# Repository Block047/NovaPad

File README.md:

# NovaPad

NovaPad is a fully customizable and open sourced macropad that I had designed for fun in my spare time.

NovaPad was designed as a multi-purpose tool, allowing for it to aid in any task at hand.

## Features
Fully customizable:
 - EC11 Rotary Encoder Switch
 - 6 Keys
 - WS2812B RGB LED's for each key
 - 128x32 OLED screens 

## Housing
The housing is split into two parts, the top lid of the case, and the lower case itself.
The PCB is secured to the case using two M3 heated inserts vertically, and the lid is secured to the case using three horizontal self-tapping screws.

Made in OnShape

## PCB

The PCB intergrates the various components included in the project, allowing them to communicate with one another, giving the keyboard its functionality.
Designing the PCB consisted of organizing the components in the positions that I wanted them in, and then drawing the trace lines, which took hours of work left untracked in hacktime (I was trying to use wakatime to track it, which ended up not working.)

## Schematic

The schematic had been the easiest part of the project, only specifying what connected to what.
The only decently difficult part of designing the schematic was figuring out where and how to get the footprints for the various components that KiCad didn't have, and figuring out how to wire the keyboard matrix.

## Firmware
This project uses KMK python code, running on the XIAO microcontroller provided by stardance flashed with CircuitPython.
The firmware leaves much for customization, the default functions only being a simple number pad with a volume knob, the OLED displaying "NovaPad".
This configuration was designed to be customized, giving the user flexability and functionality when needed.

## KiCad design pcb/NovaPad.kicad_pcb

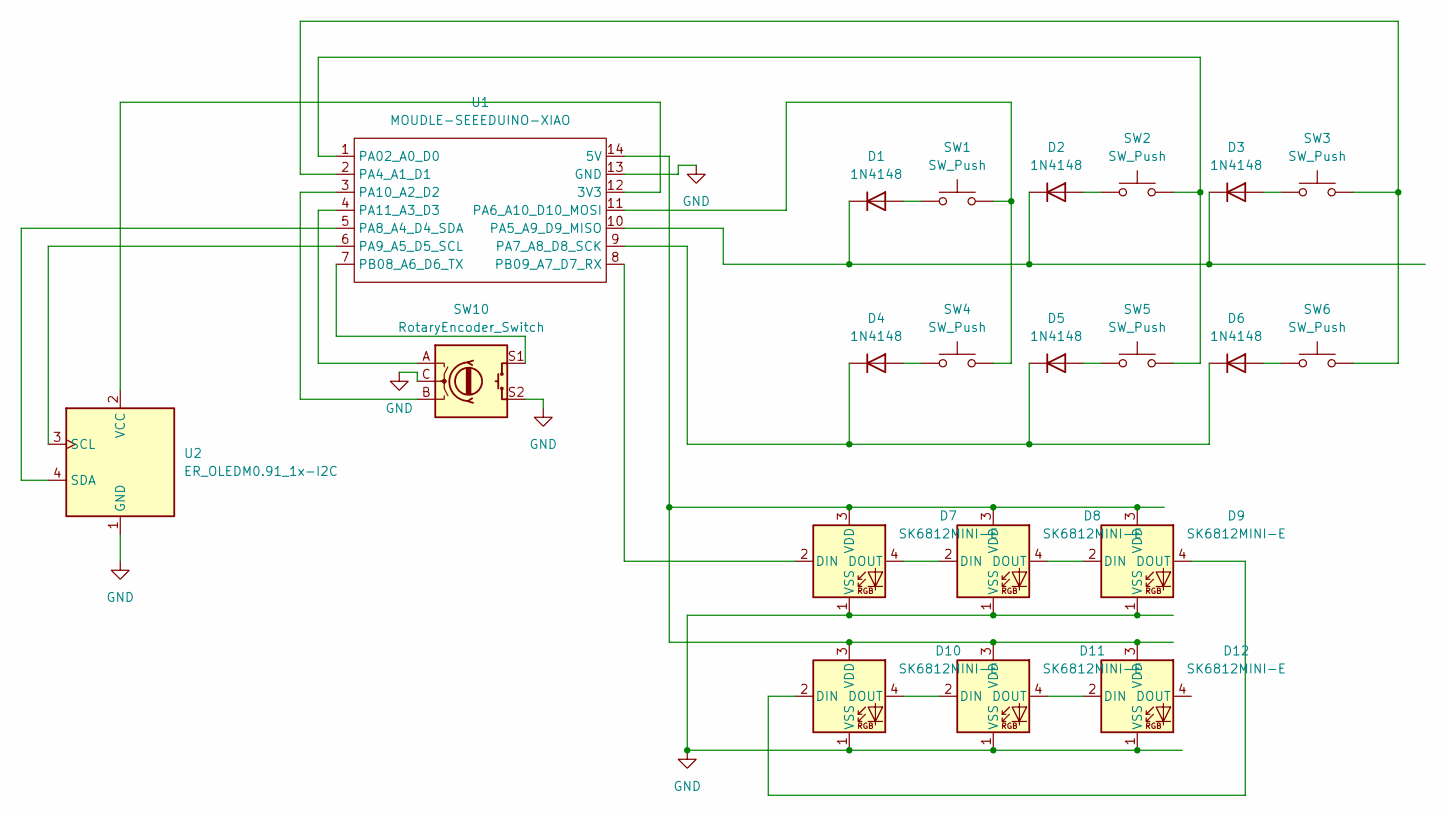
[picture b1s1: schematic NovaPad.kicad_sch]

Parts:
D1, D2, D3, D4, D5, D6: 1N4148; D_DO-35_SOD27_P7.62mm_Horizontal
D7, D8, D9, D10, D11, D12: SK6812MINI-E; LED_SK6812MINI-E_3.2x2.8mm_P1.5mm_ReverseMount
SW1, SW2, SW3, SW4, SW5, SW6: SW_Push; SW_Cherry_MX_1.00u_PCB
SW10: RotaryEncoder_Switch; RotaryEncoder_Alps_EC11E-Switch_Vertical_H20mm
U1: MOUDLE-SEEEDUINO-XIAO; XIAO-Generic-Hybrid-14P-2.54-21X17.8MM
U2: ER_OLEDM0.91_1x-I2C

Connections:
GND: D7.1 (VSS), D8.1 (VSS), D9.1 (VSS), D10.1 (VSS), D11.1 (VSS), D12.1 (VSS), SW10.C, SW10.S2, U1.13 (GND), U2.1 (GND)
unnamed: D1.2 (A), SW1.1
unnamed: D1.1 (K), D2.1 (K), D3.1 (K), U1.10 (PA5_A9_D9_MISO)
unnamed: D2.2 (A), SW2.1
unnamed: D3.2 (A), SW3.1
unnamed: D4.2 (A), SW4.1
unnamed: D4.1 (K), D5.1 (K), D6.1 (K), U1.9 (PA7_A8_D8_SCK)
unnamed: D5.2 (A), SW5.1
unnamed: D6.2 (A), SW6.1
unnamed: D7.2 (DIN), U1.8 (PB09_A7_D7_RX)
unnamed: D7.4 (DOUT), D8.2 (DIN)
unnamed: D8.4 (DOUT), D9.2 (DIN)
unnamed: D9.4 (DOUT), D10.2 (DIN)
unnamed: D10.4 (DOUT), D11.2 (DIN)
unnamed: D7.3 (VDD), D8.3 (VDD), D9.3 (VDD), D10.3 (VDD), D11.3 (VDD), D12.3 (VDD), U1.14 (5V)
unnamed: D11.4 (DOUT), D12.2 (DIN)
unnamed: U1.12 (3V3), U2.2 (VCC)
unnamed: SW2.2, SW5.2, U1.1 (PA02_A0_D0)
unnamed: SW3.2, SW6.2, U1.2 (PA4_A1_D1)
unnamed: SW1.2, SW4.2, U1.11 (PA6_A10_D10_MOSI)
unnamed: U1.5 (PA8_A4_D4_SDA), U2.4 (SDA)
unnamed: U1.6 (PA9_A5_D5_SCL), U2.3 (SCL)
unnamed: SW10.B, U1.3 (PA10_A2_D2)
unnamed: SW10.A, U1.4 (PA11_A3_D3)
unnamed: SW10.S1, U1.7 (PB08_A6_D6_TX)

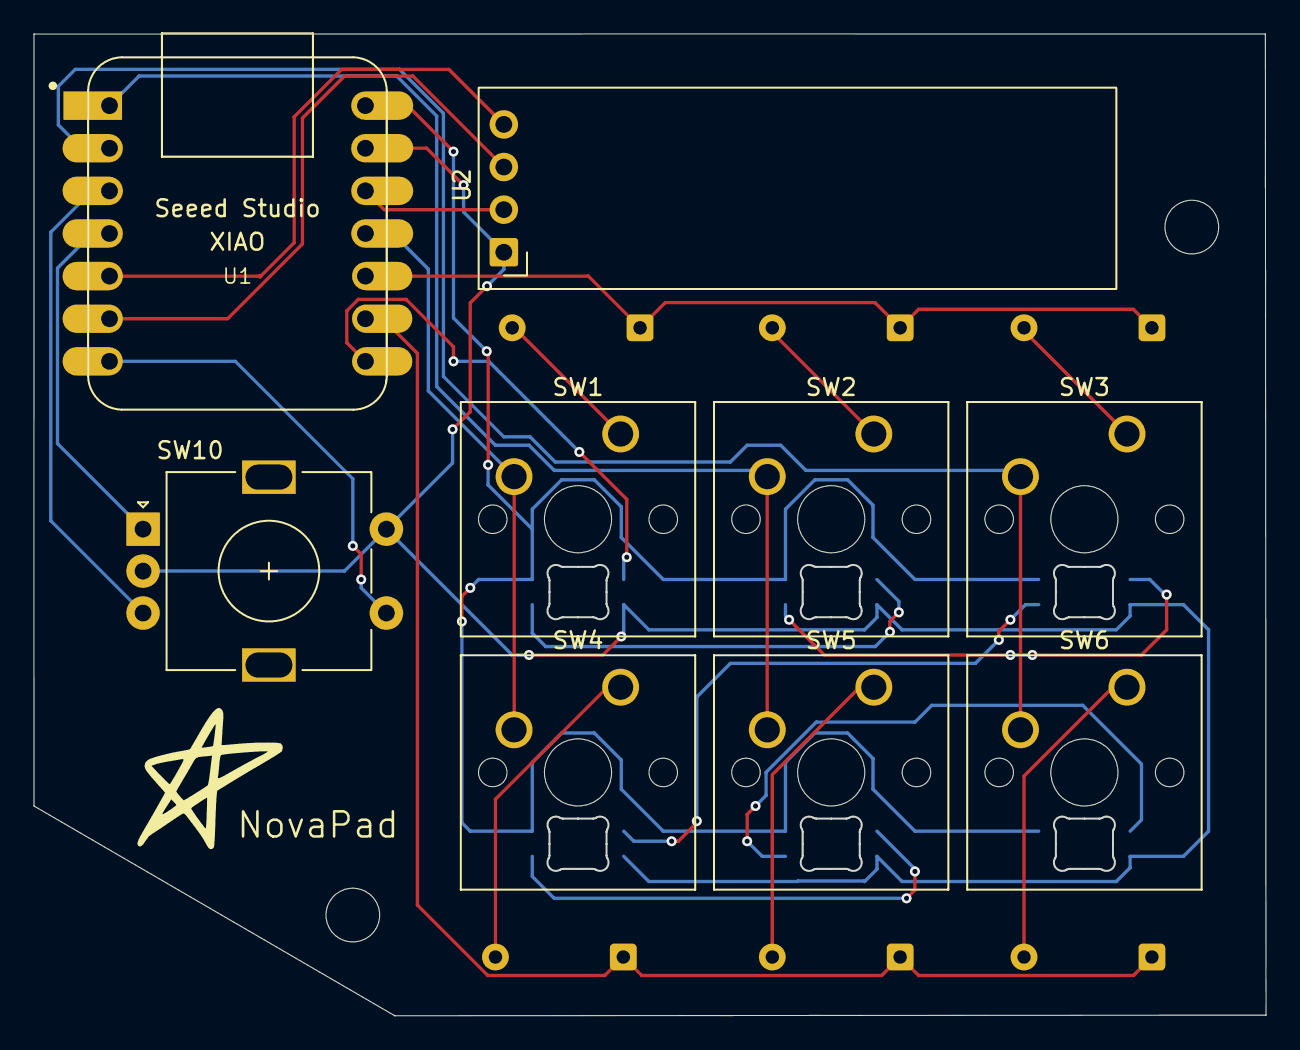
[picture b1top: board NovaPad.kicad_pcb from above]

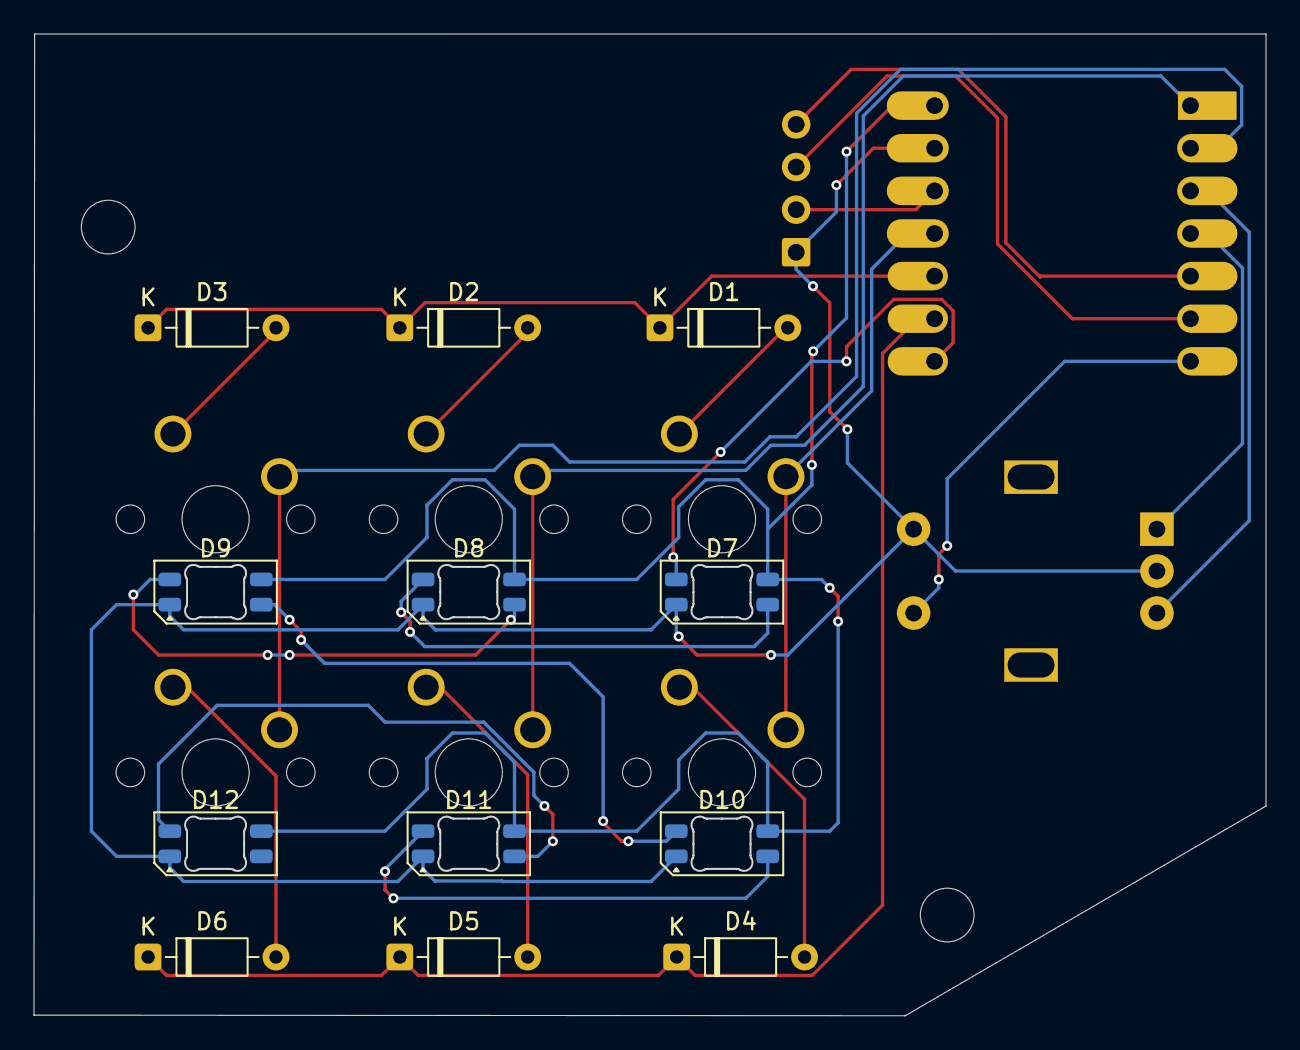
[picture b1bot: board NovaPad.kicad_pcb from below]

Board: 2 copper layers, 73.4 x 58.5 mm, 21 parts (12 on the bottom side), 25 nets.
